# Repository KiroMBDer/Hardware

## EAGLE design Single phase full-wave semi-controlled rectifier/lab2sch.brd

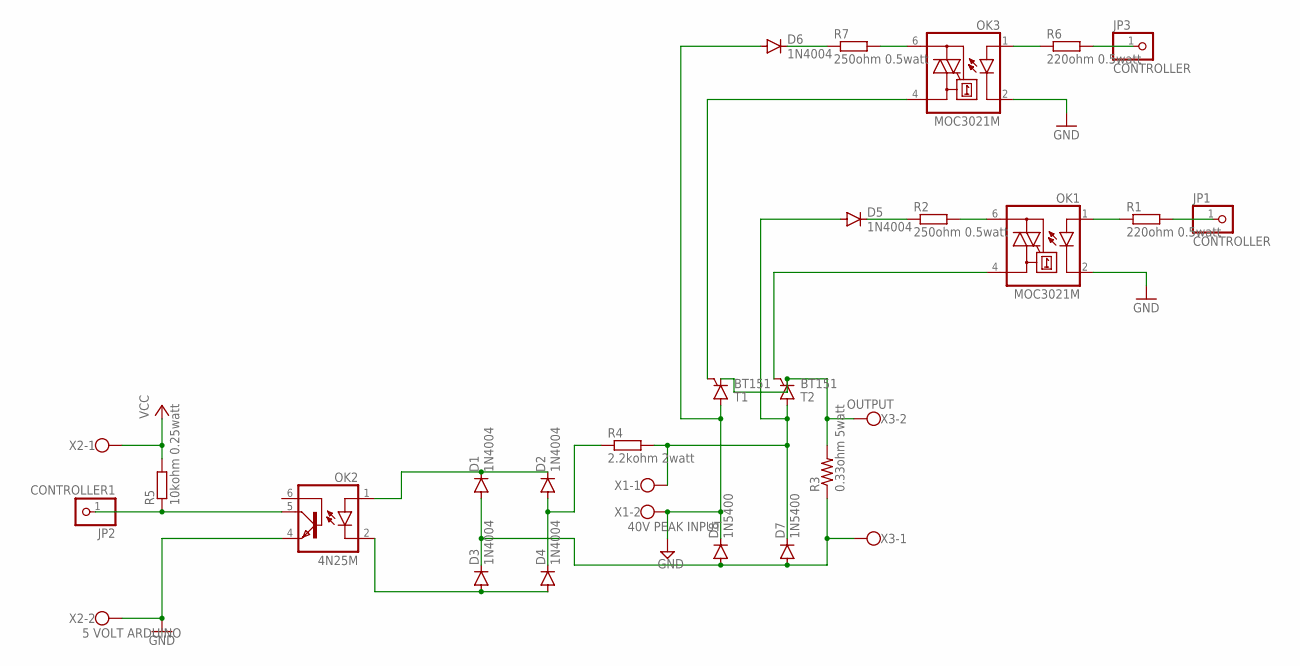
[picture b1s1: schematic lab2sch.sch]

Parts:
D1, D2, D3, D4, D5, D6: 1N4004; DO41-10
D7, D8: 1N5400; DO201-15
JP1, JP3: CONTROLLER; 1X01
JP2: CONTROLLER1; 1X01
OK1, OK3: MOC3021M; DIL06
OK2: 4N25M; DIL06
R1, R6: 220ohm 0.5watt; 0204/7
R2, R7: 250ohm 0.5watt; 0207/10
R3: 0.33ohm 5watt; 0617/22
R4: 2.2kohm 2watt; 0204/7
R5: 10kohm 0.25watt; 0204/7
T1, T2: BT151; TO220CL
X1: 40V PEAK INPUT; W237-102
X2: 5 VOLT ARDUINO; W237-102
X3: OUTPUT; W237-102

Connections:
GND: D6.A, D8.C, OK1.2 (C), OK2.4 (EMI), OK3.2 (C), T1.A, X1.2, X2.2
unnamed: OK1.1 (A), R1.1
unnamed: OK1.6 (A2), R2.2
unnamed: D5.C, R2.1
unnamed: OK1.4 (A1), T2.G
unnamed: R3.2, T1.C, T2.C, X3.2
unnamed: D3.A, D4.A, OK2.2 (C)
unnamed: D1.C, D2.C, OK2.1 (A)
unnamed: D2.A, D4.C, R4.1
unnamed: D1.A, D3.C, D7.A, D8.A, R3.1, X3.1
unnamed: JP1.1, R1.2
unnamed: OK3.1 (A), R6.1
unnamed: JP2.1, OK2.5 (COL), R5.1
unnamed: OK3.6 (A2), R7.2
unnamed: D6.C, R7.1
unnamed: OK3.4 (A1), T1.G
unnamed: JP3.1, R6.2
unnamed: D5.A, D7.C, R4.2, T2.A, X1.1
VCC: R5.2, X2.1

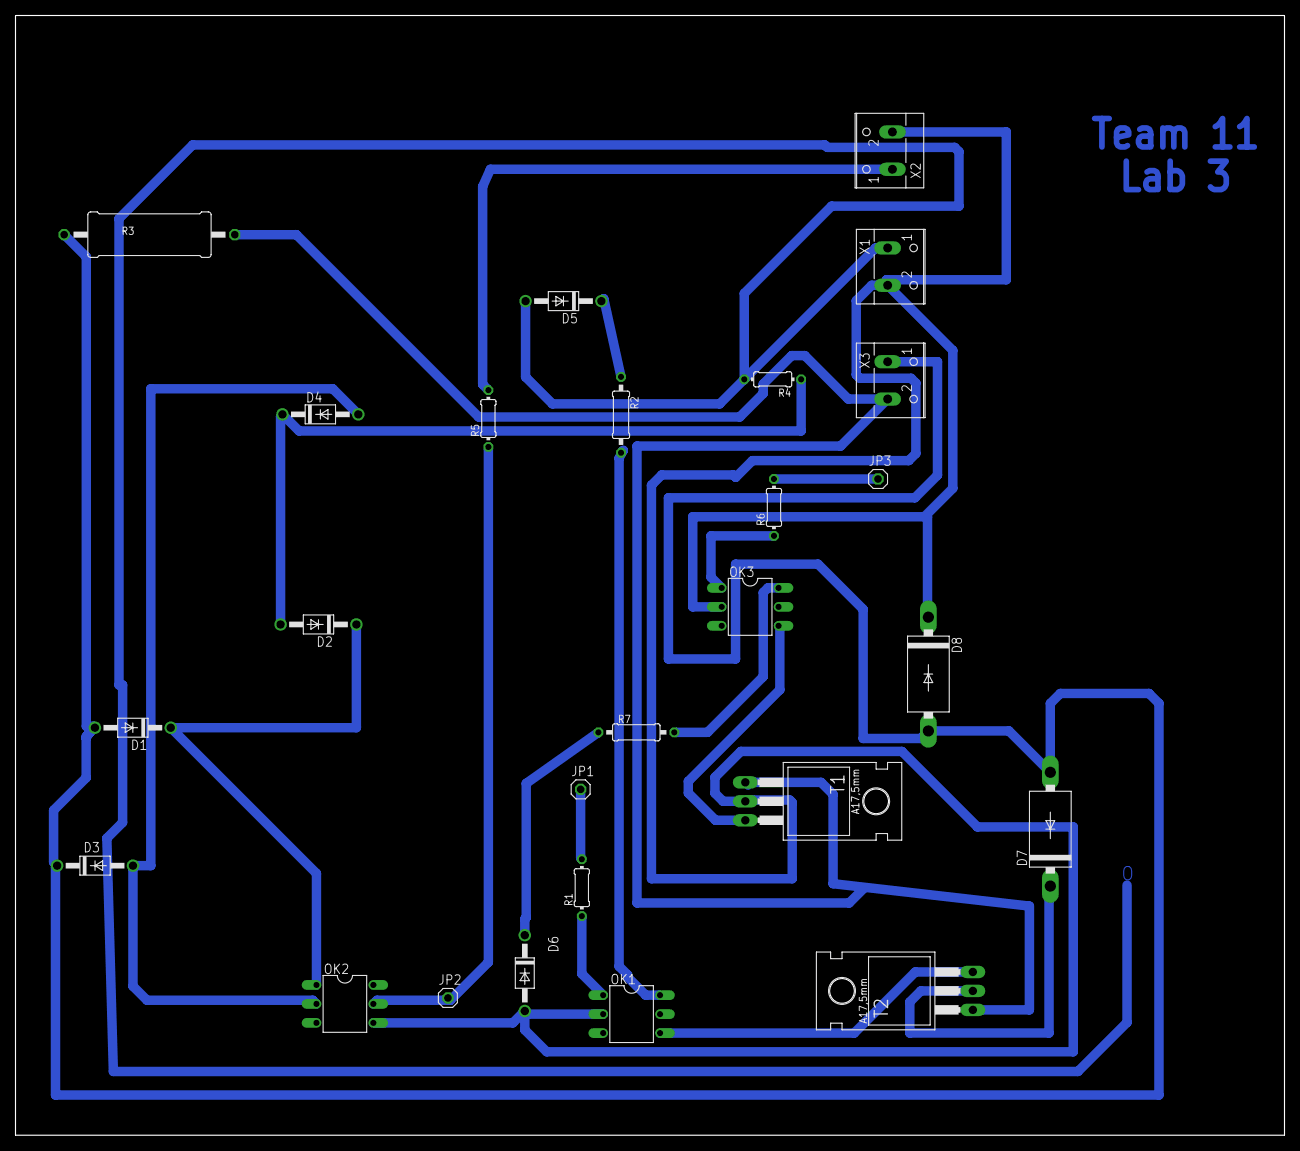
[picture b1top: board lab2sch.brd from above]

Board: 2 copper layers, 170.0 x 150.0 mm, 26 parts (0 on the bottom side), 19 nets.
